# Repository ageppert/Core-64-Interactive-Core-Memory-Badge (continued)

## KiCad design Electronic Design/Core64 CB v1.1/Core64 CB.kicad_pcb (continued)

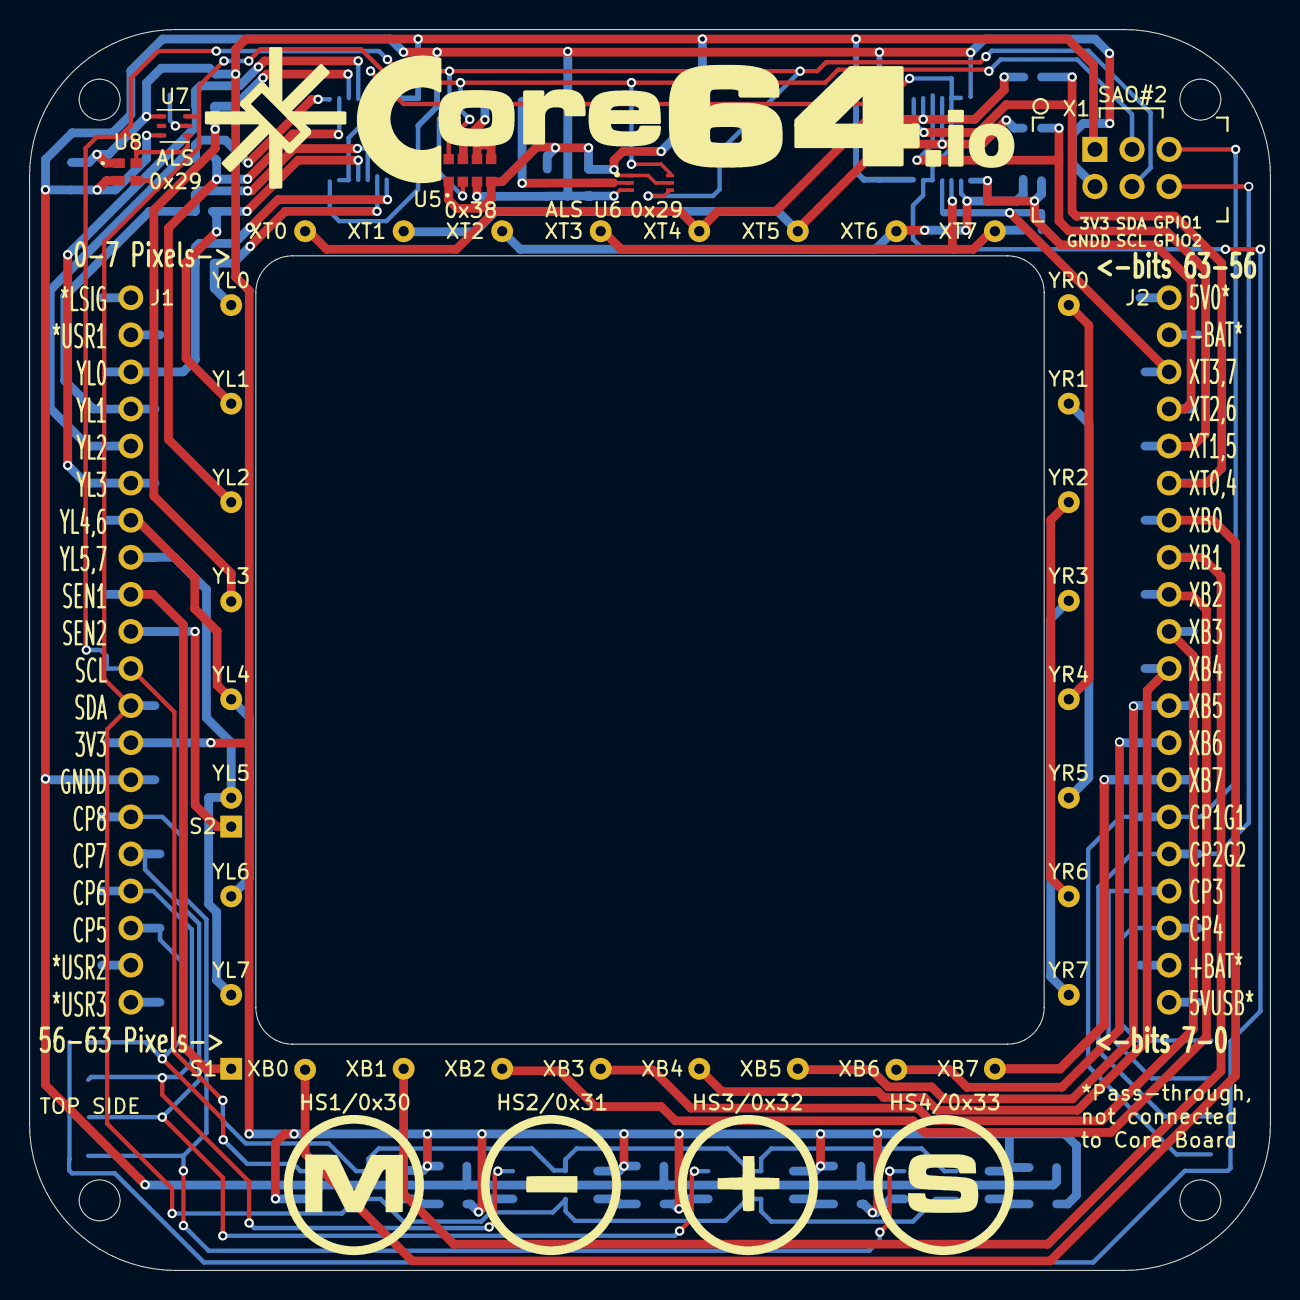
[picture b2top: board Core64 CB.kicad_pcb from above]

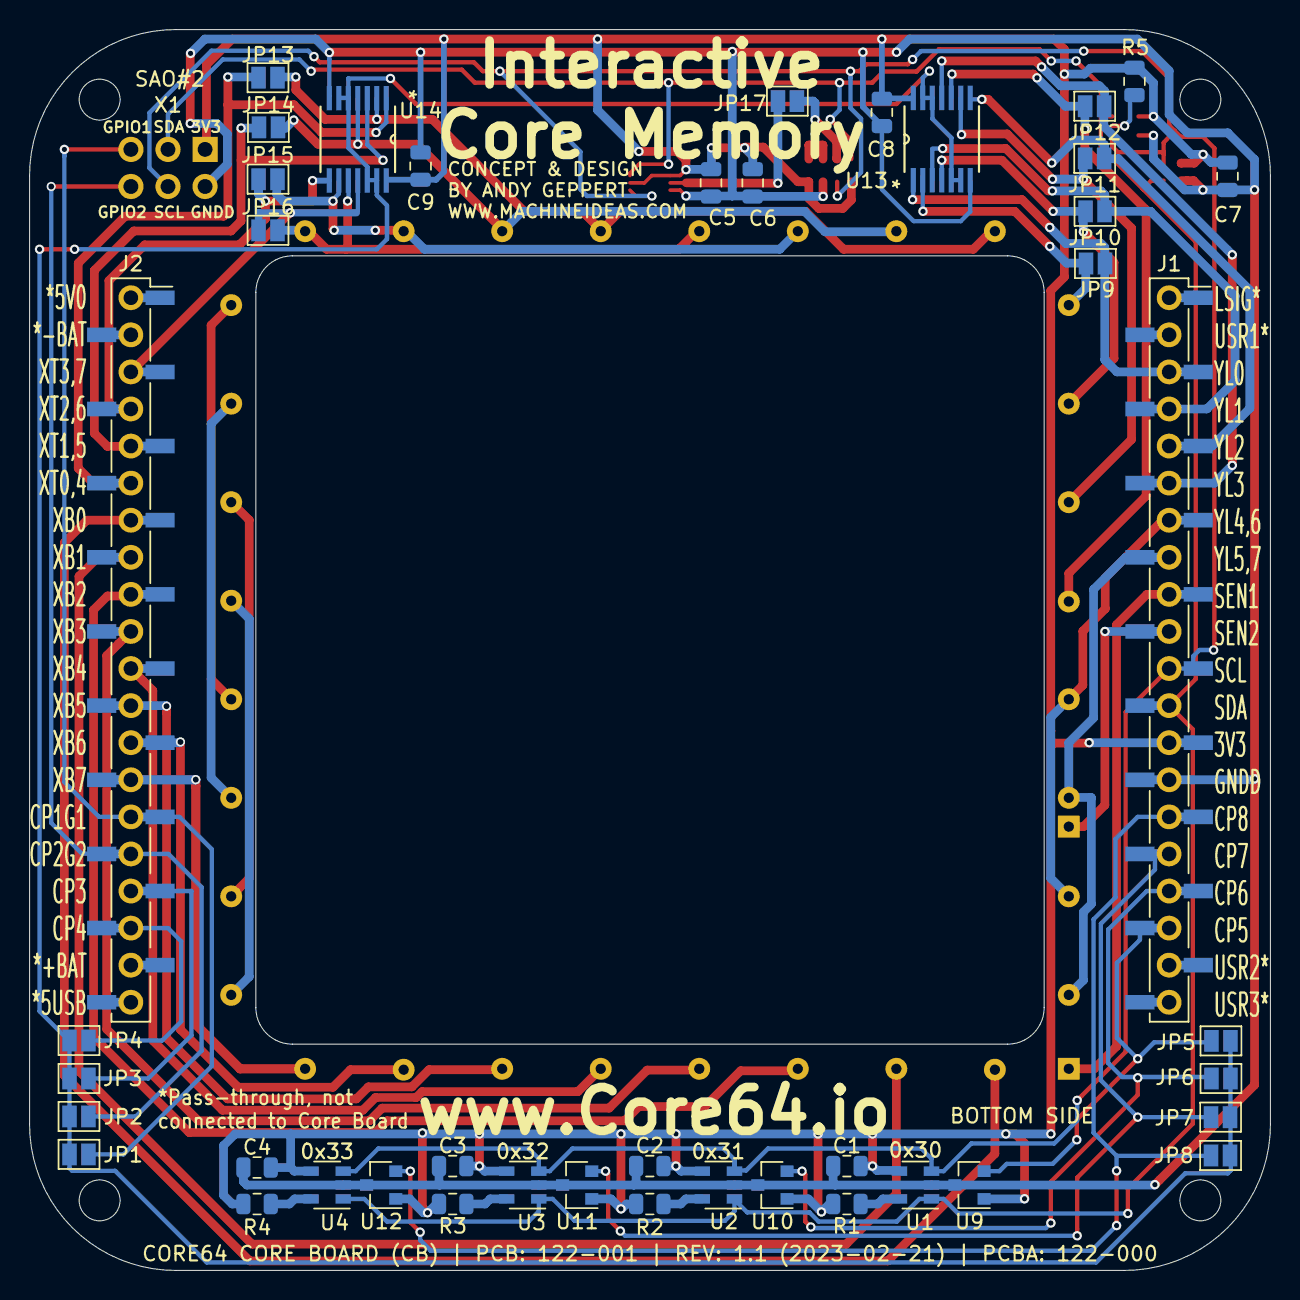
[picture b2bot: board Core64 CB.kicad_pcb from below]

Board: 2 copper layers, 85.0 x 85.0 mm, 51 parts (43 on the bottom side), 53 nets.

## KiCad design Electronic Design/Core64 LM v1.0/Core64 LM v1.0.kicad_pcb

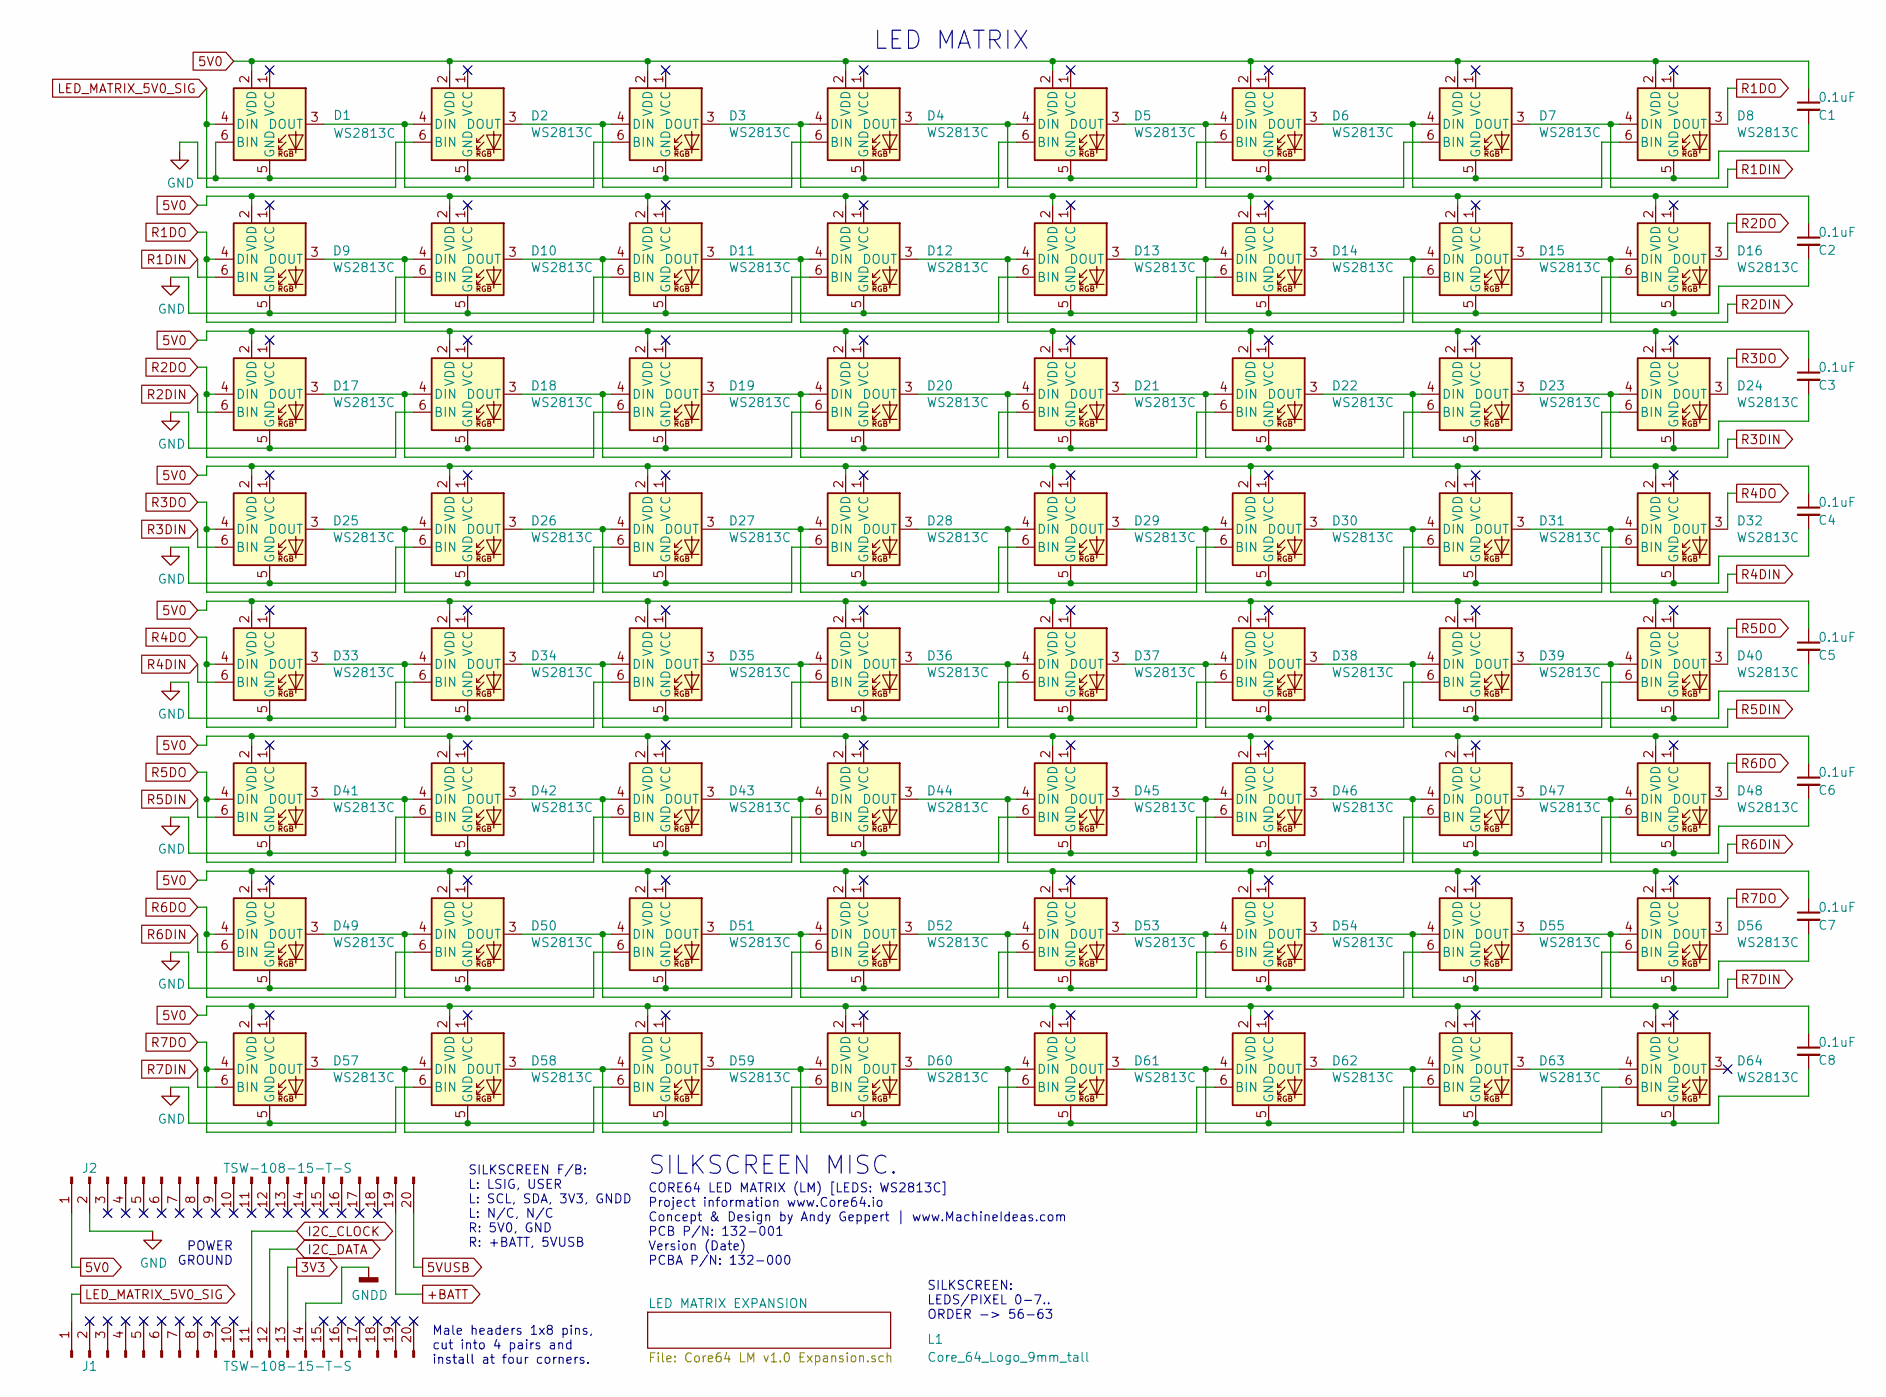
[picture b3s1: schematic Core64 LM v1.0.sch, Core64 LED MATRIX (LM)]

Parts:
C1, C2, C3, C4, C5, C6, C7, C8: 0.1uF; C_0603_1608Metric; Mfr P/N CC0603KRX7R9BB104; JLCPCB P/N C14663
D1, D2, D3, D4, D5, D6, D7, D8, D9, D10, D11, D12, D13, D14, D15, D16, D17, D18, D19, D20, D21, D22, D23, D24, D25, D26, D27, D28, D29, D30, D31, D32, D33, D34, D35, D36, D37, D38, D39, D40, D41, D42, D43, D44, D45, D46, D47, D48, D49, D50, D51, D52, D53, D54, D55, D56, D57, D58, D59, D60, D61, D62, D63, D64: WS2813C; LED_WS2813_PLCC6_5.0x5.0mm_P1.6mm_Core64_Abg_Mod; JLCPCB P/N C194323
J1, J2: TSW-108-15-T-S; PinHeader_1x20_P2.54mm_Vertical_SMD_and_TH_Pin1Right; Mfr P/N TSW-108-15-T-S
L1: Core_64_Logo_9mm_tall; Core64_Logo_9mm_tall

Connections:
3V3: J1.13; also elsewhere on the board
5V0: C1.1, C2.1, C3.1, C4.1, C5.1, C6.1, C7.1, C8.1, D1.2 (VDD), D2.2 (VDD), D3.2 (VDD), D4.2 (VDD), D5.2 (VDD), D6.2 (VDD), D7.2 (VDD), D8.2 (VDD), D9.2 (VDD), D10.2 (VDD), D11.2 (VDD), D12.2 (VDD), D13.2 (VDD), D14.2 (VDD), D15.2 (VDD), D16.2 (VDD), D17.2 (VDD), D18.2 (VDD), D19.2 (VDD), D20.2 (VDD), D21.2 (VDD), D22.2 (VDD), D23.2 (VDD), D24.2 (VDD), D25.2 (VDD), D26.2 (VDD), D27.2 (VDD), D28.2 (VDD), D29.2 (VDD), D30.2 (VDD), D31.2 (VDD), D32.2 (VDD), D33.2 (VDD), D34.2 (VDD), D35.2 (VDD), D36.2 (VDD), D37.2 (VDD), D38.2 (VDD), D39.2 (VDD), D40.2 (VDD), D41.2 (VDD), D42.2 (VDD), D43.2 (VDD), D44.2 (VDD), D45.2 (VDD), D46.2 (VDD), D47.2 (VDD), D48.2 (VDD), D49.2 (VDD), D50.2 (VDD), D51.2 (VDD), D52.2 (VDD), D53.2 (VDD), D54.2 (VDD), D55.2 (VDD), D56.2 (VDD), D57.2 (VDD), D58.2 (VDD), D59.2 (VDD), D60.2 (VDD), D61.2 (VDD), D62.2 (VDD), D63.2 (VDD), D64.2 (VDD), J2.1; also elsewhere on the board
5VUSB: J2.20; also elsewhere on the board
+BATT: J2.19; also elsewhere on the board
GND: C1.2, C2.2, C3.2, C4.2, C5.2, C6.2, C7.2, C8.2, D1.5 (GND), D1.6 (BIN), D2.5 (GND), D3.5 (GND), D4.5 (GND), D5.5 (GND), D6.5 (GND), D7.5 (GND), D8.5 (GND), D9.5 (GND), D10.5 (GND), D11.5 (GND), D12.5 (GND), D13.5 (GND), D14.5 (GND), D15.5 (GND), D16.5 (GND), D17.5 (GND), D18.5 (GND), D19.5 (GND), D20.5 (GND), D21.5 (GND), D22.5 (GND), D23.5 (GND), D24.5 (GND), D25.5 (GND), D26.5 (GND), D27.5 (GND), D28.5 (GND), D29.5 (GND), D30.5 (GND), D31.5 (GND), D32.5 (GND), D33.5 (GND), D34.5 (GND), D35.5 (GND), D36.5 (GND), D37.5 (GND), D38.5 (GND), D39.5 (GND), D40.5 (GND), D41.5 (GND), D42.5 (GND), D43.5 (GND), D44.5 (GND), D45.5 (GND), D46.5 (GND), D47.5 (GND), D48.5 (GND), D49.5 (GND), D50.5 (GND), D51.5 (GND), D52.5 (GND), D53.5 (GND), D54.5 (GND), D55.5 (GND), D56.5 (GND), D57.5 (GND), D58.5 (GND), D59.5 (GND), D60.5 (GND), D61.5 (GND), D62.5 (GND), D63.5 (GND), D64.5 (GND), J2.2; also elsewhere on the board
GNDD: J1.14; also elsewhere on the board
I2C_CLOCK: J1.11; also elsewhere on the board
I2C_DATA: J1.12; also elsewhere on the board
LED_MATRIX_5V0_SIG: D1.4 (DIN), D2.6 (BIN), J1.1
unnamed: D1.3 (DOUT), D2.4 (DIN), D3.6 (BIN)
unnamed: D2.3 (DOUT), D3.4 (DIN), D4.6 (BIN)
unnamed: D3.3 (DOUT), D4.4 (DIN), D5.6 (BIN)
unnamed: D4.3 (DOUT), D5.4 (DIN), D6.6 (BIN)
unnamed: D5.3 (DOUT), D6.4 (DIN), D7.6 (BIN)
unnamed: D6.3 (DOUT), D7.4 (DIN), D8.6 (BIN)
unnamed: D10.3 (DOUT), D11.4 (DIN), D12.6 (BIN)
unnamed: D9.3 (DOUT), D10.4 (DIN), D11.6 (BIN)
unnamed: D11.3 (DOUT), D12.4 (DIN), D13.6 (BIN)
unnamed: D12.3 (DOUT), D13.4 (DIN), D14.6 (BIN)
unnamed: D13.3 (DOUT), D14.4 (DIN), D15.6 (BIN)
unnamed: D14.3 (DOUT), D15.4 (DIN), D16.6 (BIN)
unnamed: D17.3 (DOUT), D18.4 (DIN), D19.6 (BIN)
unnamed: D18.3 (DOUT), D19.4 (DIN), D20.6 (BIN)
unnamed: D19.3 (DOUT), D20.4 (DIN), D21.6 (BIN)
unnamed: D20.3 (DOUT), D21.4 (DIN), D22.6 (BIN)
unnamed: D21.3 (DOUT), D22.4 (DIN), D23.6 (BIN)
unnamed: D22.3 (DOUT), D23.4 (DIN), D24.6 (BIN)
unnamed: D25.3 (DOUT), D26.4 (DIN), D27.6 (BIN)
unnamed: D26.3 (DOUT), D27.4 (DIN), D28.6 (BIN)
unnamed: D27.3 (DOUT), D28.4 (DIN), D29.6 (BIN)
unnamed: D28.3 (DOUT), D29.4 (DIN), D30.6 (BIN)
unnamed: D29.3 (DOUT), D30.4 (DIN), D31.6 (BIN)
unnamed: D30.3 (DOUT), D31.4 (DIN), D32.6 (BIN)
unnamed: D33.3 (DOUT), D34.4 (DIN), D35.6 (BIN)
unnamed: D34.3 (DOUT), D35.4 (DIN), D36.6 (BIN)
unnamed: D35.3 (DOUT), D36.4 (DIN), D37.6 (BIN)
unnamed: D36.3 (DOUT), D37.4 (DIN), D38.6 (BIN)
unnamed: D37.3 (DOUT), D38.4 (DIN), D39.6 (BIN)
unnamed: D38.3 (DOUT), D39.4 (DIN), D40.6 (BIN)
unnamed: D41.3 (DOUT), D42.4 (DIN), D43.6 (BIN)
unnamed: D42.3 (DOUT), D43.4 (DIN), D44.6 (BIN)
unnamed: D43.3 (DOUT), D44.4 (DIN), D45.6 (BIN)
unnamed: D44.3 (DOUT), D45.4 (DIN), D46.6 (BIN)
unnamed: D45.3 (DOUT), D46.4 (DIN), D47.6 (BIN)
unnamed: D46.3 (DOUT), D47.4 (DIN), D48.6 (BIN)
unnamed: D49.3 (DOUT), D50.4 (DIN), D51.6 (BIN)
unnamed: D50.3 (DOUT), D51.4 (DIN), D52.6 (BIN)
unnamed: D51.3 (DOUT), D52.4 (DIN), D53.6 (BIN)
unnamed: D52.3 (DOUT), D53.4 (DIN), D54.6 (BIN)
unnamed: D53.3 (DOUT), D54.4 (DIN), D55.6 (BIN)
unnamed: D54.3 (DOUT), D55.4 (DIN), D56.6 (BIN)
unnamed: D57.3 (DOUT), D58.4 (DIN), D59.6 (BIN)
unnamed: D58.3 (DOUT), D59.4 (DIN), D60.6 (BIN)
unnamed: D59.3 (DOUT), D60.4 (DIN), D61.6 (BIN)
unnamed: D60.3 (DOUT), D61.4 (DIN), D62.6 (BIN)
unnamed: D61.3 (DOUT), D62.4 (DIN), D63.6 (BIN)
unnamed: D62.3 (DOUT), D63.4 (DIN), D64.6 (BIN)
unnamed: D63.3 (DOUT), D64.4 (DIN)
R1DIN: D7.3 (DOUT), D8.4 (DIN), D9.6 (BIN)
R1DO: D8.3 (DOUT), D9.4 (DIN), D10.6 (BIN)
R2DIN: D15.3 (DOUT), D16.4 (DIN), D17.6 (BIN)
R2DO: D16.3 (DOUT), D17.4 (DIN), D18.6 (BIN)
R3DIN: D23.3 (DOUT), D24.4 (DIN), D25.6 (BIN)
R3DO: D24.3 (DOUT), D25.4 (DIN), D26.6 (BIN)
R4DIN: D31.3 (DOUT), D32.4 (DIN), D33.6 (BIN)
R4DO: D32.3 (DOUT), D33.4 (DIN), D34.6 (BIN)
R5DIN: D39.3 (DOUT), D40.4 (DIN), D41.6 (BIN)
R5DO: D40.3 (DOUT), D41.4 (DIN), D42.6 (BIN)
R6DIN: D47.3 (DOUT), D48.4 (DIN), D49.6 (BIN)
R6DO: D48.3 (DOUT), D49.4 (DIN), D50.6 (BIN)
R7DIN: D55.3 (DOUT), D56.4 (DIN), D57.6 (BIN)
R7DO: D56.3 (DOUT), D57.4 (DIN), D58.6 (BIN)

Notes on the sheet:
SILKSCREEN F/B: L: LSIG, USER L: SCL, SDA, 3V3, GNDD L: N/C, N/C R: 5V0, GND R: +BATT, 5VUSB
POWER GROUND
LED MATRIX
SILKSCREEN: LEDS/PIXEL 0-7.. ORDER -> 56-63
CORE64 LED MATRIX (LM) [LEDS: WS2813C] Project information www.Core64.io Concept & Design by Andy Geppert | www.MachineIdeas.com PCB P/N: 132-001 Version (Date) PCBA P/N: 132-000
SILKSCREEN MISC.
Male headers 1x8 pins, cut into 4 pairs and install at four corners.

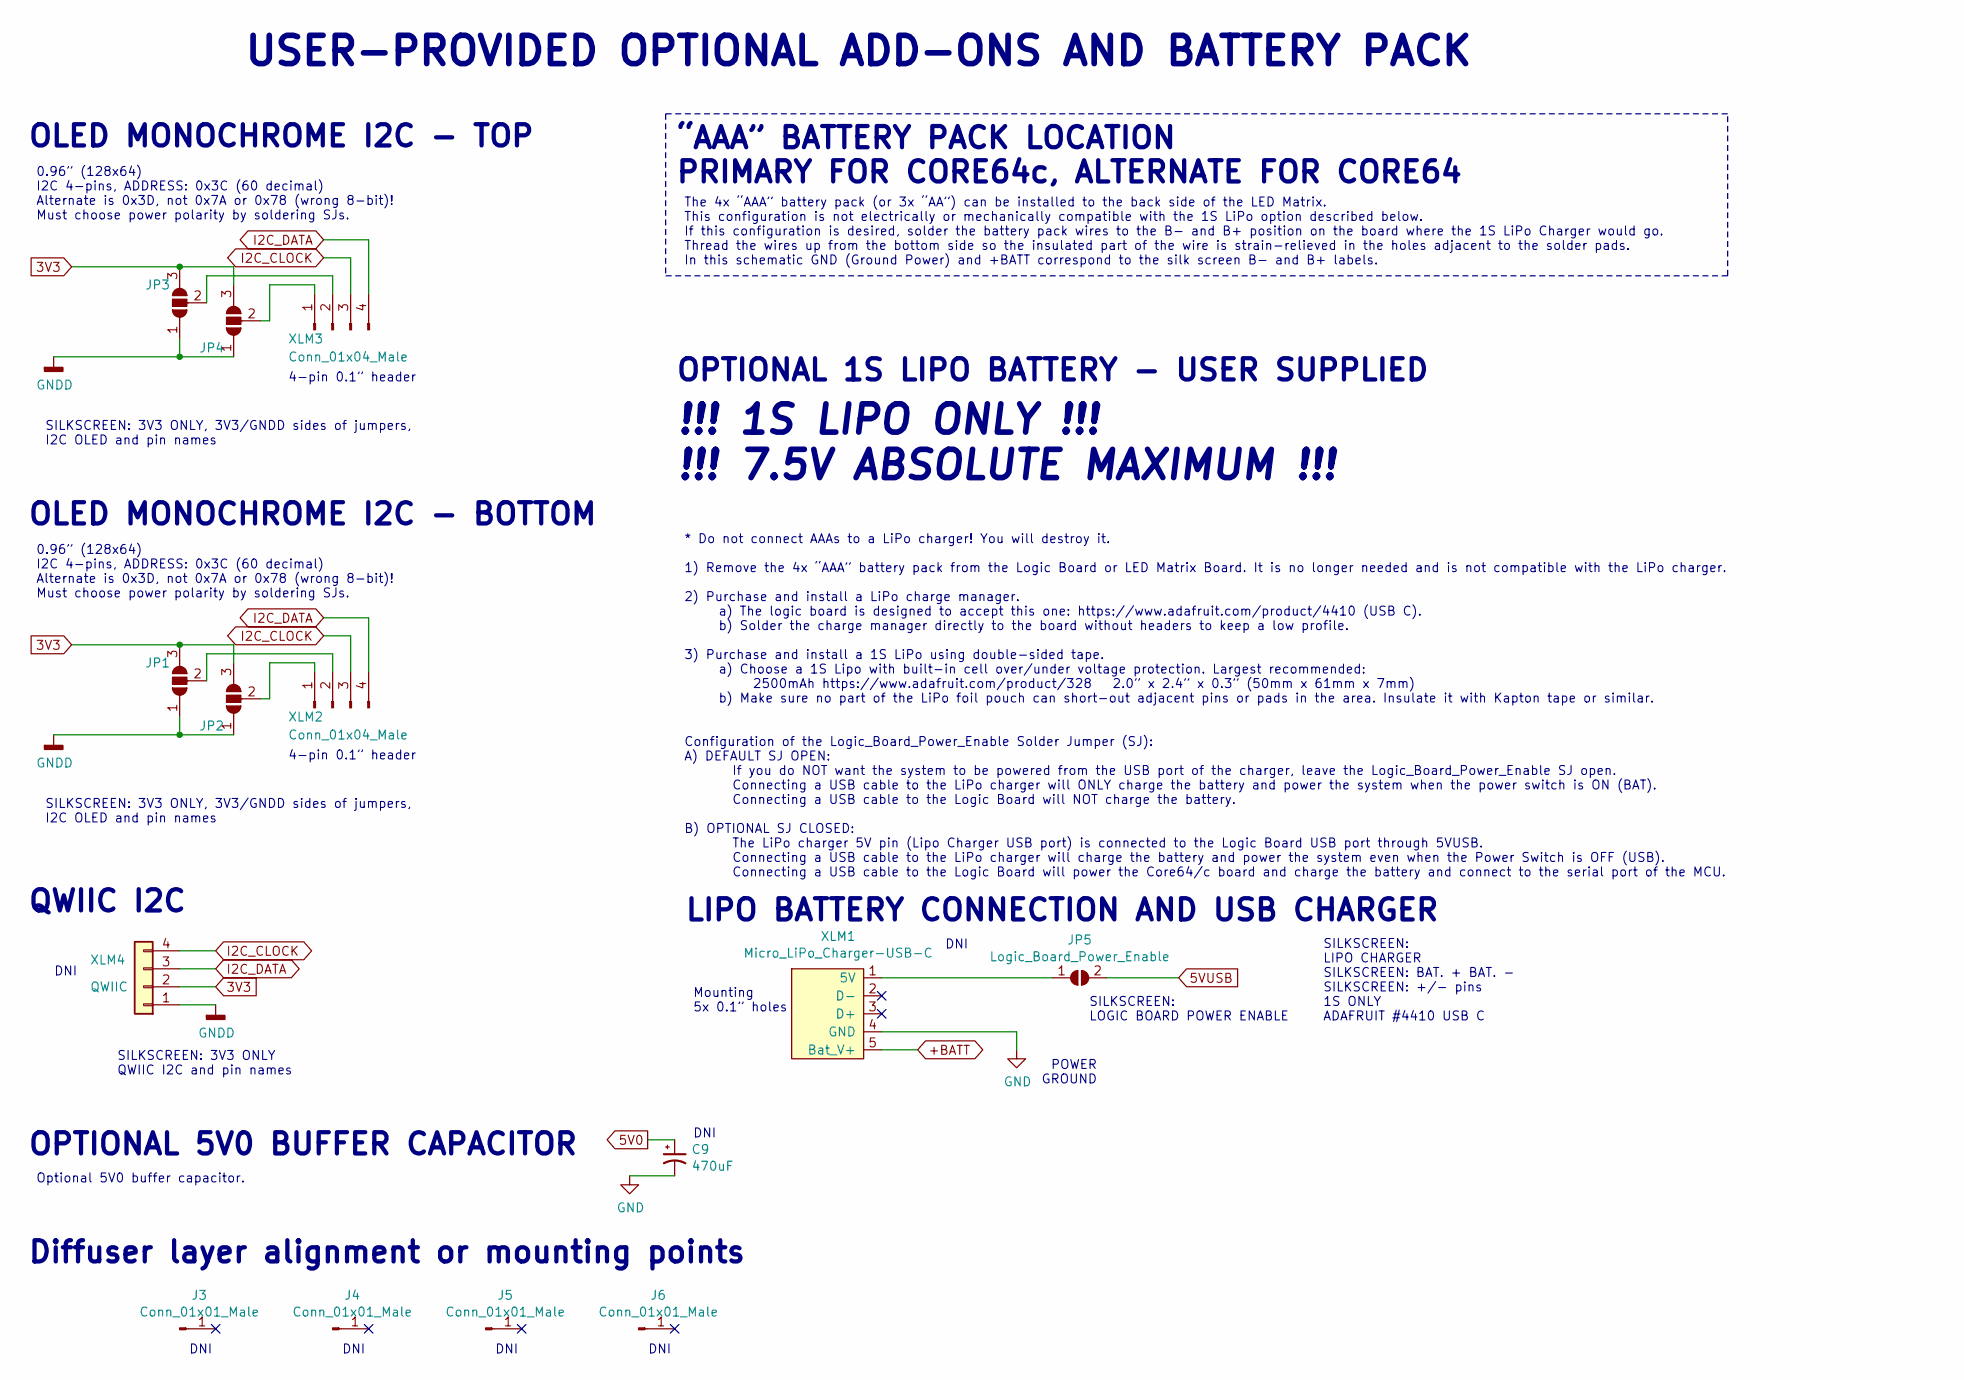
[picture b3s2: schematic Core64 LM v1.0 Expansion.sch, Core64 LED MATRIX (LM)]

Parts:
C9: 470uF; CP_Elec_6.3x7.7
J3, J4, J5, J6: Conn_01x01_Male; PinHeader_1x01_P2.54mm_Vertical_No_Registration
JP1, JP2, JP3, JP4: SolderJumper_3_Open; SolderJumper-3_P1.3mm_Open_Pad1.0x1.5mm_NumberLabels
JP5: Logic_Board_Power_Enable; SolderJumper-2_P1.3mm_Open_Pad1.0x1.5mm
XLM1: Micro_LiPo_Charger-USB-C; Micro_LiPo_Charger_USB-C_CornerSMD
XLM2, XLM3: Conn_01x04_Male; PinHeader_1x04_P2.54mm_Vertical
XLM4: QWIIC; JST_SH_SM04B-SRSS-TB_1x04-1MP_P1.00mm_Horizontal

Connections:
3V3: JP1.3 (B), JP2.3 (B), JP3.3 (B), JP4.3 (B), XLM4.2; also elsewhere on the board
5V0: C9.1; also elsewhere on the board
5VUSB: JP5.2 (B); also elsewhere on the board
+BATT: XLM1.5 (Bat_V+); also elsewhere on the board
GND: C9.2, XLM1.4 (GND); also elsewhere on the board
GNDD: JP1.1 (A), JP2.1 (A), JP3.1 (A), JP4.1 (A), XLM4.1; also elsewhere on the board
I2C_CLOCK: XLM2.3, XLM3.3, XLM4.4; also elsewhere on the board
I2C_DATA: XLM2.4, XLM3.4, XLM4.3; also elsewhere on the board
unnamed: JP1.2 (C), XLM2.2
unnamed: JP2.2 (C), XLM2.1
unnamed: JP3.2 (C), XLM3.2
unnamed: JP4.2 (C), XLM3.1
unnamed: JP5.1 (A), XLM1.1 (5V)

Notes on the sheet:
OLED MONOCHROME I2C - TOP
0.96” (128x64) I2C 4-pins, ADDRESS: 0x3C (60 decimal) Alternate is 0x3D, not 0x7A or 0x78 (wrong 8-bit)! Must choose power polarity by soldering SJs.
QWIIC I2C
SILKSCREEN: 3V3 ONLY, 3V3/GNDD sides of jumpers, I2C OLED and pin names
4-pin 0.1” header
SILKSCREEN: 3V3 ONLY QWIIC I2C and pin names
POWER GROUND
LIPO BATTERY CONNECTION AND USB CHARGER
USER-PROVIDED OPTIONAL ADD-ONS AND BATTERY PACK
OPTIONAL 1S LIPO BATTERY - USER SUPPLIED
!!! 1S LIPO ONLY !!! !!! 7.5V ABSOLUTE MAXIMUM !!!
SILKSCREEN: LIPO CHARGER SILKSCREEN: BAT. + BAT. - SILKSCREEN: +/- pins 1S ONLY ADAFRUIT #4410 USB C
Mounting 5x 0.1” holes
* Do not connect AAAs to a LiPo charger! You will destroy it. 1) Remove the 4x “AAA” battery pack from the Logic Board or LED Matrix Board. It is no longer needed and is not compatible with the LiPo charger. 2) Purchase and install a LiPo charge manager. a) The logic board is designed to accept thi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
OLED MONOCHROME I2C - BOTTOM
SILKSCREEN: LOGIC BOARD POWER ENABLE
Diffuser layer alignment or mounting points
“AAA” BATTERY PACK LOCATION PRIMARY FOR CORE64c, ALTERNATE FOR CORE64
The 4x “AAA” battery pack (or 3x “AA”) can be installed to the back side of the LED Matrix. This configuration is not electrically or mechanically compatible with the 1S LiPo option described below. If this configuration is desired, solder the battery pack wires to the B- and B+ position on the boa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
OPTIONAL 5V0 BUFFER CAPACITOR
Optional 5V0 buffer capacitor.
DNI

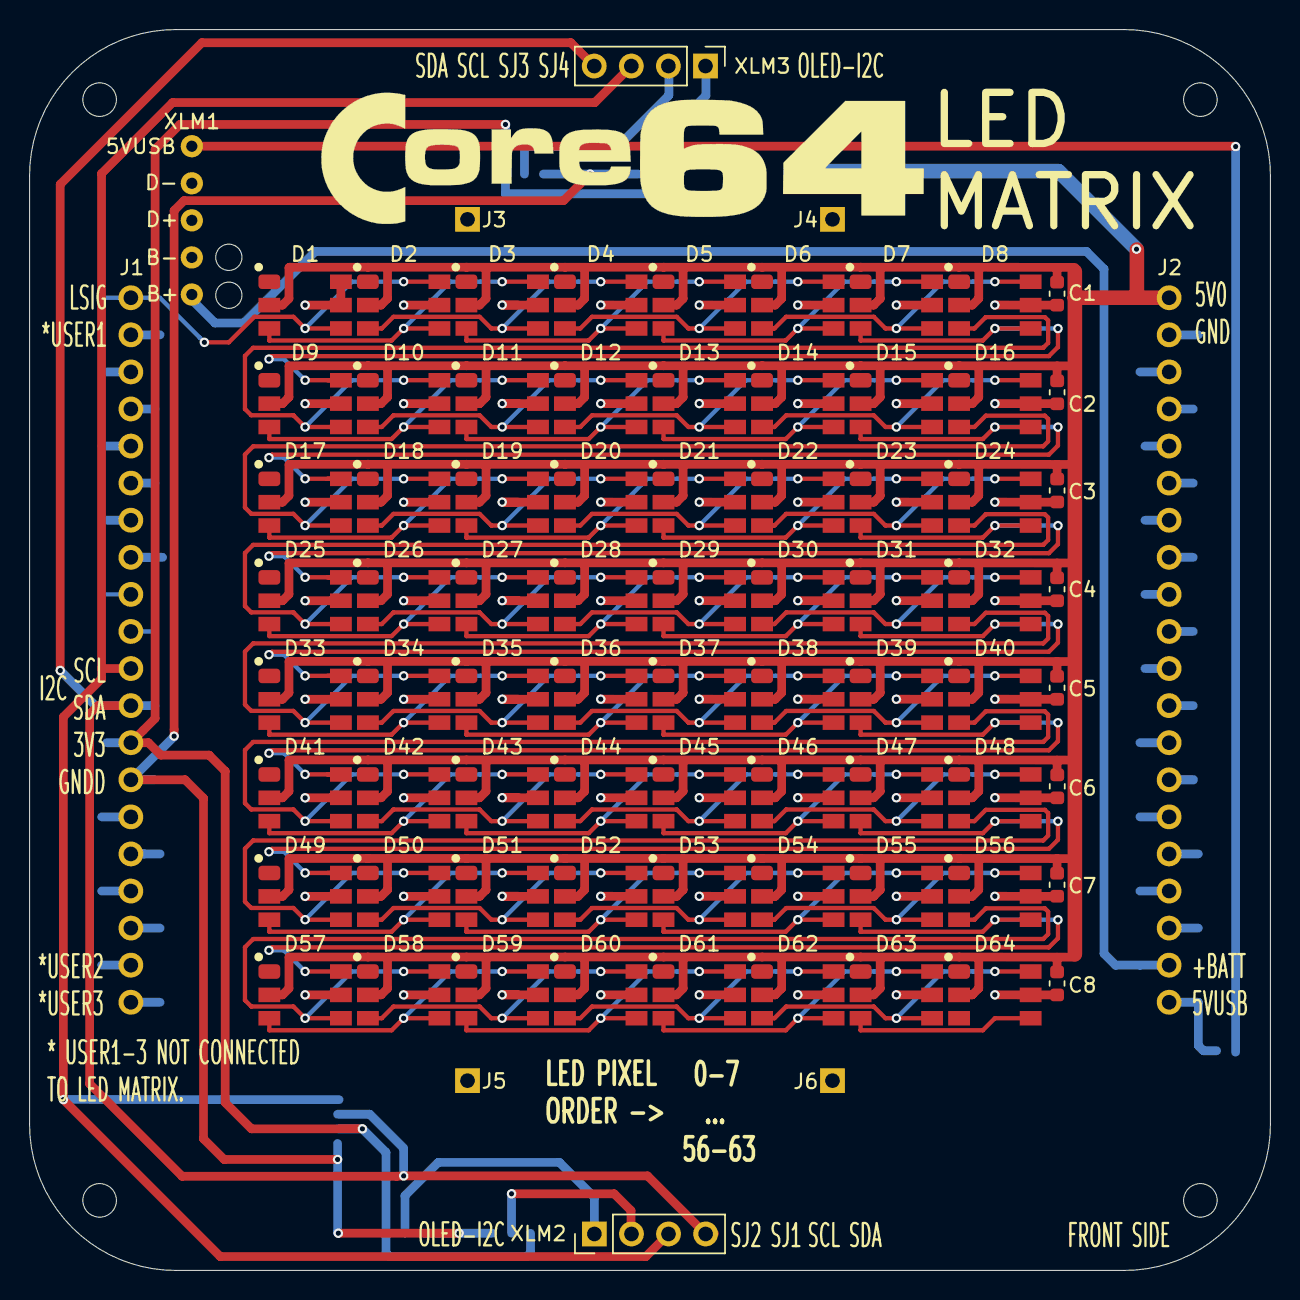
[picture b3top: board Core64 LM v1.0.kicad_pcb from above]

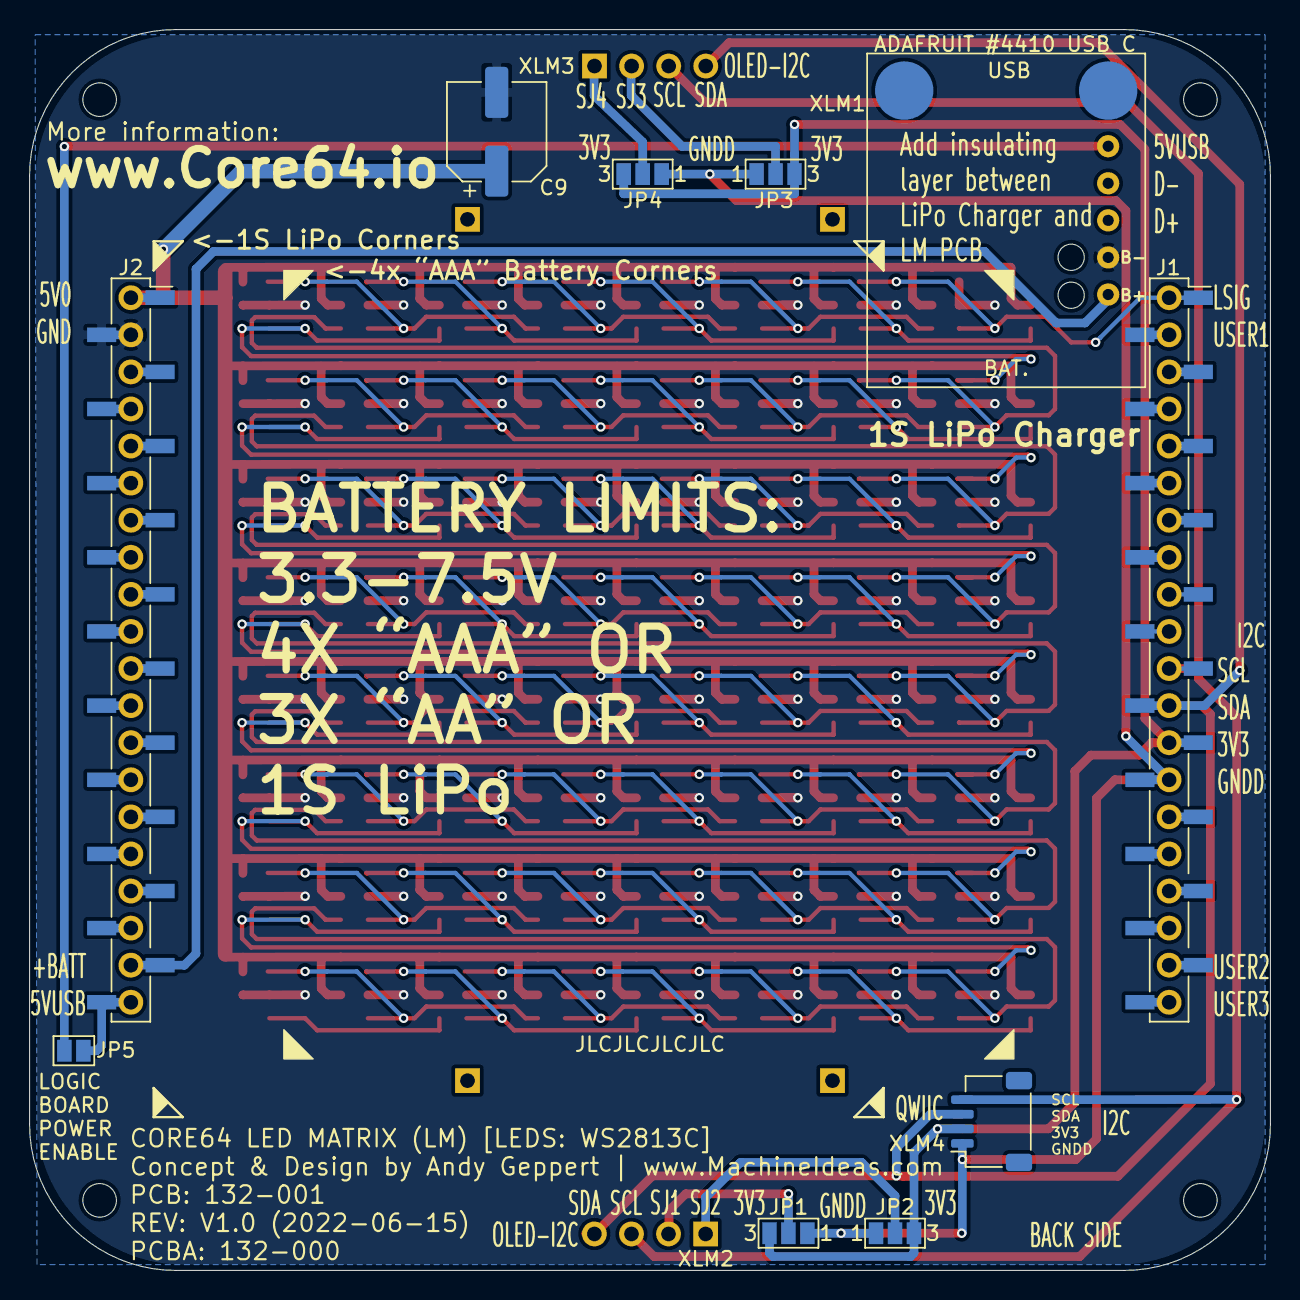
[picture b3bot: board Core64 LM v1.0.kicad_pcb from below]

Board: 2 copper layers, 85.0 x 85.0 mm, 89 parts (10 on the bottom side), 77 nets.

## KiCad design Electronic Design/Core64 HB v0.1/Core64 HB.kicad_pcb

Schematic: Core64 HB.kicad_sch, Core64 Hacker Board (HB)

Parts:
H1, H2: GND PAD; MountingHole_3.2mm_M3_Pad_Via
JP1, JP2: SolderJumper_3_Open; SolderJumper-3_P1.3mm_Open_RoundedPad1.0x1.5mm_NumberLabels
JP7: D2; SolderJumper-2_P1.3mm_Open_RoundedPad1.0x1.5mm
JP8: D1; SolderJumper-2_P1.3mm_Open_RoundedPad1.0x1.5mm
L1, L2: Core_64_Logo; Core64.io_w_core_symbol
X2: SSW-104-22-L-S-VS; PinSocket_1x04_P2.54mm_Vertical
X3, X7: HEADER_30-PIN_0.1; PinSocket_1x30_P2.54mm_Vertical
X5: HEADER_11-PIN_0.1; PinSocket_1x11_P2.54mm_Vertical
X6: Header_11-PIN_0.1; PinSocket_1x11_P2.54mm_Vertical
X8: SAO_conn_SFH11-NBPC-D03-ST-BK; Badgelife-SAOv169-BADGE-2x3; MPN SFH11-NBPC-D03-ST-BK
X9: QWIIC; JST_SH_SM04B-SRSS-TB_1x04-1MP_P1.00mm_Horizontal; LCSC C160404
X31, X71: DNI; PinSocket_1x30_P2.54mm_Vertical

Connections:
3V3: JP1.3 (B), JP2.3 (B), X6.1, X7.6, X8.1 (3V3), X9.2, X71.6
5V0: X5.10, X7.5, X71.5
-BATT: H1.1, H2.1, JP1.1 (A), JP2.1 (A), X5.11, X6.2, X7.2, X7.30, X8.2 (GND), X9.1, X71.2, X71.30
/5VM: X7.23, X71.23
/5VUSB: X7.3, X71.3
/+BATT: X7.1, X71.1
/+VSW: X7.4, X71.4
/ADC0_BUFF: X7.22, X71.22
/ADC1_BUFF: JP8.2 (B), X7.24, X71.24
/ADC2_BUFF: JP7.2 (B), X7.25, X71.25
/BC0_MON: X7.27, X71.27
/CM_EN: X3.6, X31.6
/CM_Q1N: X3.11, X31.11
/CM_Q1P: X3.12, X31.12
/CM_Q2N: X3.13, X31.13
/CM_Q2P: X3.14, X31.14
/CM_Q3N: X3.15, X31.15
/CM_Q3P: X3.16, X31.16
/CM_Q4N: X3.17, X31.17
/CM_Q4P: X3.18, X31.18
/CM_Q5N: X3.19, X31.19
/CM_Q5P: X3.20, X31.20
/CM_Q6N: X3.21, X31.21
/CM_Q6P: X3.22, X31.22
/CM_Q7N: X3.23, X31.23
/CM_Q7P: X3.24, X31.24
/CM_Q8N: X3.25, X31.25
/CM_Q8P: X3.26, X31.26
/CM_Q9N: X3.27, X31.27
/CM_Q9P: X3.28, X31.28
/CM_Q10N: X3.29, X31.29
/CM_Q10P: X3.30, X31.30
/CM_SENSE_PULSE: X3.4, X31.4
/CM_SENSE_RESET: X3.5, X31.5
/CM_SR_CLK: X3.8, X31.8
/CM_SR_LAT: X3.9, X31.9
/CM_SR_SER1: X3.7, X31.7
/CM_SR_~OE: X3.10, X31.10
/D1: JP8.1 (A), X6.7
/D2: JP7.1 (A), X6.8
/GPIO1_CP1_SAO1: X7.8, X8.5 (GPIO1), X71.8
/GPIO2_CP2_SAO2: X7.9, X8.6 (GPIO2), X71.9
/GPIO3_CP3_DC: X5.3, X7.10, X71.10
/GPIO4_CP4_CS2: X5.5, X6.11, X7.11, X71.11
/GPIO5_CP5_HS1: X7.12, X71.12
/GPIO6_CP6_HS2: X7.13, X71.13
/GPIO7_CP7_HS3: X7.14, X71.14
/GPIO8_CP8_HS4: X7.15, X71.15
/I2C_3V3_SCL: X2.3, X3.1, X8.4 (SCL), X9.4, X31.1
/I2C_3V3_SDA: X2.4, X3.2, X8.3 (SDA), X9.3, X31.2
/LED_ARY_3V3_SIG: X3.3, X31.3
/LR0_MON: X7.28, X71.28
/PICO_3V3OUT: X7.7, X71.7
/RR0_MON: X7.29, X71.29
/SPI_CD: X5.8, X6.9, X7.17, X71.17
/SPI_CLK: X5.2, X6.3, X7.21, X71.21
/SPI_CS1: X5.6, X6.6, X7.18, X71.18
/SPI_RESET: X5.4, X6.10, X7.16, X71.16
/SPI_SDI: X5.7, X6.4, X7.19, X71.19
/SPI_SDO: X5.1, X6.5, X7.20, X71.20
/TC0_MON: X7.26, X71.26
unnamed: JP1.2 (C), X2.2
unnamed: JP2.2 (C), X2.1

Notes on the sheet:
SILKSCREEN FRONT
AMBIENT PROX. SENSOR OLED AND!XOR IO Exp. MCP23017 AND!XOR EEPROM AT24C32r NFC CLICK PN7120
SPI
USER PORT A
https://hackaday.io/project/175182-simple-add-ons-sao using Sullins SFH11-NBPC-D03-ST-BK female header https://www.digikey.com/product-detail/en/sullins-connector-solutions/ SFH11-NBPC-D03-ST-BK/S9717-ND/4558818
SAO #1 SIMPLE ADD-ONS
COPI
Both SPI chip select lines are may be pulled high with resistors on the Logic Board. Some Logic Boards do not include the pull-up resistors.
0x29 (47) 0x30 (48) 0x31 (49) 0x32 (50) 0x33 (51) 0x57 (87)
These headers are available on the Hacker Board and are wired in parallel to the same port that is on the Logic Board and Hacker Board. USER PORT A USER PORT B OLED MONOCHROME I2C OLED COLOR SPI W/MICRO SD MICRO SD CARD, SPI (the D1 and D2 pins are shared with analog pins) SAO #1 QWIIC I2C Two of t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
POWER
ANALOG
OLED COLOR SPI W/MICRO SD
Adafruit #4682
SILKSCREEN: 3V3 Logic ONLY, 3V3/GND sides of jumpers, SPI OLED
Compatible with https://www.adafruit.com/product/4682 (pins 1-6, 9) MicroSD card standalone pins shared between TFT and OLED boards.
AMBIENT LIGHT SENSOR HALL SENSOR 1 HALL SENSOR 2 HALL SENSOR 3 HALL SENSOR 4 EEPROM (BOARD ID)
CS OLED
CIPO
Compatible: https://www.adafruit.com/product/1431 1.5” 128x128, 16-bit color w/MicroSD holder OLED has 5V -> 3V3 regulator onboard. MicroSD card standalone pins shared between TFT and OLED boards.
HACKER PLAYGROUND
3-7.5V MAX
SILKSCREEN: 3V3 ONLY, 3V3/GND sides of jumpers, I2C OLED and pin names
CORE MATRIX DRIVER QXY
I2C ADDRESS TABLE
OLED ON THIS SIDE OF HEADER -TOP VIEW OF LB
2x GND PAD 3.2 mm (.125 in) thru-hole for M3 or #4 screw
Generic 0.96” (128x64) or 1.5” (128x128) I2C 4-pins, often ADDRESS: 0x3C (60 decimal) Alternate is 0x3D, not 0x7A or 0x78 (wrong 8-bit)! Must choose power polarity by soldering SJS.
0.1" PIN GRID
CORE MATRIX DRIVE IO EXPANSION
USER-PROVIDED OPTIONAL ADD-ONS SEE CORE64 HACKER GUIDE
CA ENABLE
GPIO/CPS
SYSTEM GROUNDS
LED ARRAY
CARD ON THIS SIDE OF HEADER
MICRO SD CARD, SPI
Some of the spare IO on the Logic Board is not accessible on the Hacker Board: Spare SR Shift Register Outputs A, B, C, D If you intend to directly drive the Core Matrix Transistors (CM_QxN and CM_QyP) you need to make sure the Shift Registers outputs do not interfere. To set those outputs to a hig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
USER PORT B
Spare

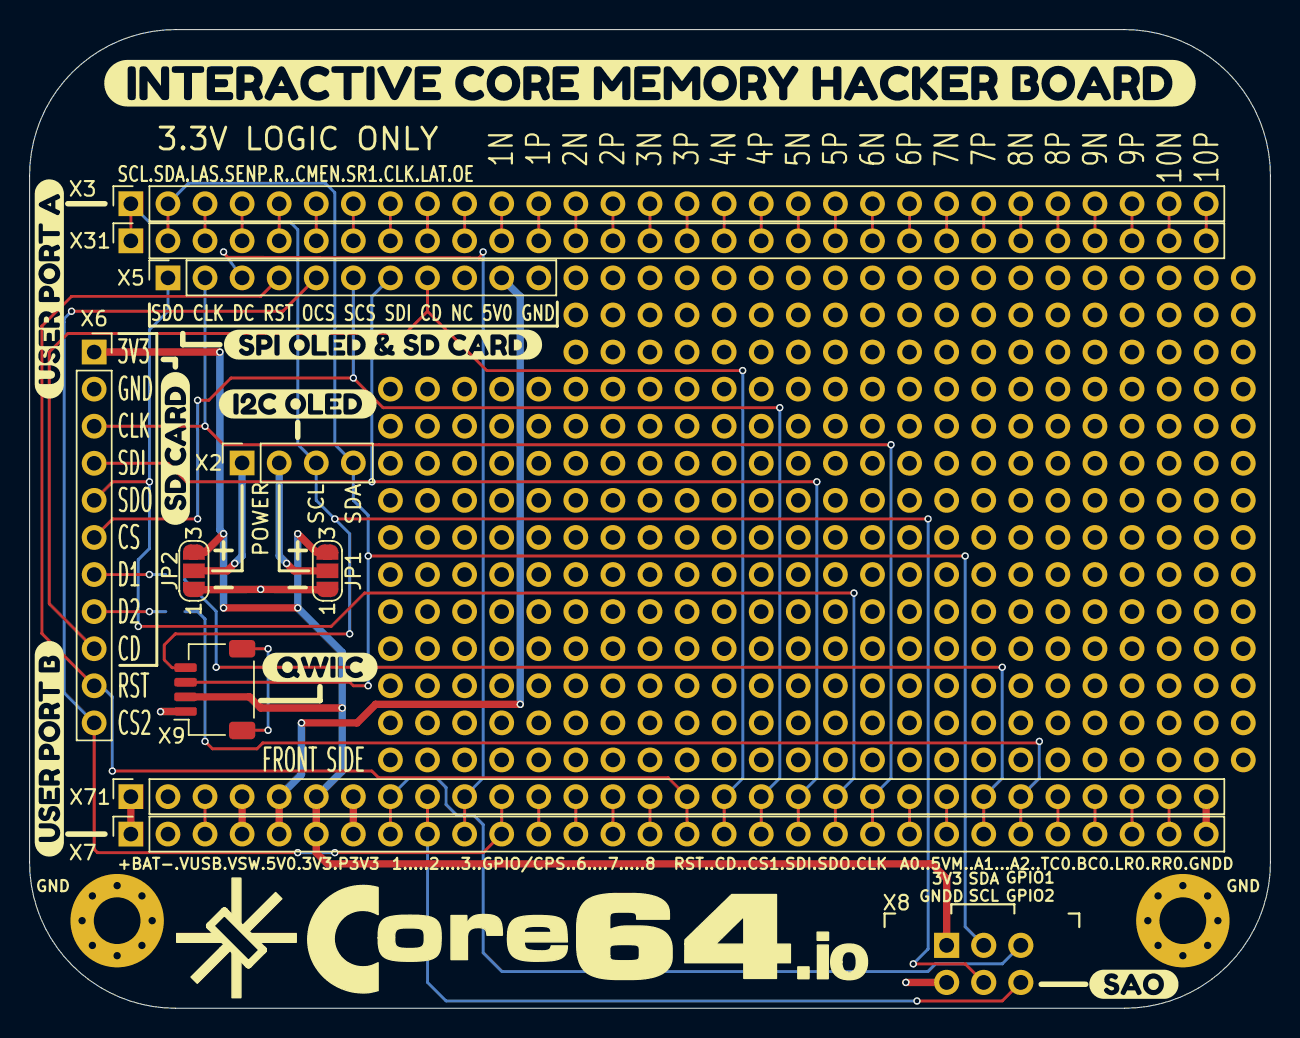
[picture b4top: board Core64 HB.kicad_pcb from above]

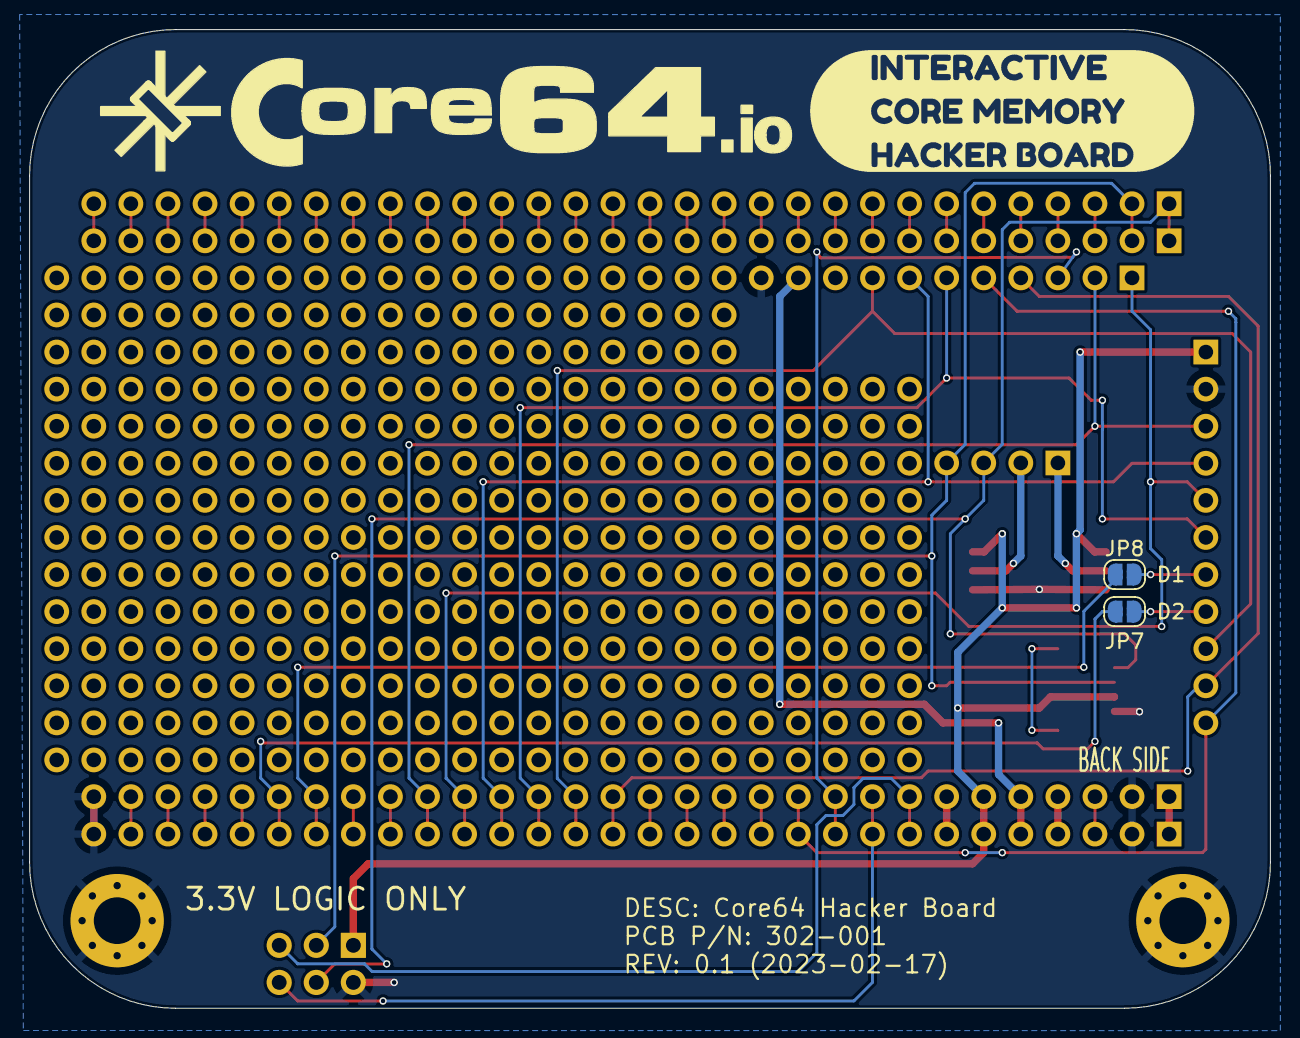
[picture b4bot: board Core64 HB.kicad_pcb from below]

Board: 2 copper layers, 85.0 x 67.0 mm, 26 parts (4 on the bottom side), 63 nets.

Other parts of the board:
kibuzzard-63DD6D83: G***; kibuzzard-63DD6D83
kibuzzard-63DD6DA7: G***; kibuzzard-63DD6DA7
kibuzzard-63DD6DEE: G***; kibuzzard-63DD6DEE
kibuzzard-63DD6FFD: G***; kibuzzard-63DD6FFD
kibuzzard-63DD70A9: G***; kibuzzard-63DD70A9
kibuzzard-63DD721E: G***; kibuzzard-63DD721E
kibuzzard-63DD735C: G***; kibuzzard-63DD735C
kibuzzard-63EEE4D8: G***; kibuzzard-63EEE4D8
kibuzzard-63EEE6A3: G***; kibuzzard-63EEE6A3
